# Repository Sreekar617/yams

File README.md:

## Yet Another Metronome by Sreekar  

Usually when I'm practicing my violin, I like to do a lot of metronome work to keep myself on tempo. However, neither my phone nor my laptop can be heard above the sound of the violin, and it's generally not a good idea to practice quieter because you practice the way you perform.  

Up until this point, my solution was to use the metronome on a Roland Digital Piano, since they're super loud and available for use at my school, where I do most of my practice. The problem is, I don't always practice in the practice rooms, and even then, the rooms with the piano aren't always available.  

My solution is to make a small, portable metronome that can stil get loud enough to hear over my violin playing. The device contains a piezo buzzer, a single Neopixel for visual feedback, an OLED to see the current BPM, and a rotary encoder to change the BPM. To keep things light and small, it's powered by a XIAO RP2040. 

PCB                             |  PCB + Case
:------------------------------:|:---------------------------------:
| 

BOM:
| Id | Designator | Footprint                                      | Quantity | Designation           | Supplier and ref | Link                                                                     |
| -- | ---------- | ---------------------------------------------- | -------- | --------------------- | ---------------- | ------------------------------------------------------------------------ |
| 1  | D1         | LED_SK6812MINI_PLCC4_3.5x3.5mm_P1.75mm         | 1        | SK6812MINI            | C5149201         | https://jlcpcb.com/partdetail/OPSCOOptoelectronics-SK6812MINIE/C5149201  |
| 2  | Q1         | SOT-23                                         | 1        | Q_NPN_BEC             | C2150            | https://jlcpcb.com/partdetail/2507-SS8050_RANGE_200_350/C2150            |
| 3  | J1         | OLED_128x32                                    | 1        | OLED_128x32           | C5248081         | https://jlcpcb.com/partdetail/HS-HS91L02W2C01/C5248081                   |
| 4  | SW1        | RotaryEncoder_Alps_EC11E-Switch_Vertical_H20mm | 1        | RotaryEncoder_Switch  | C202365          | https://jlcpcb.com/partdetail/ALPSALPINE-EC11E18244AU/C202365            |
| 5  | R1         | R_0603_1608Metric                              | 1        | 300Ω                  | C23025           | https://jlcpcb.com/partdetail/23752-0603WAF3000T5E/C23025                |
| 6  | R2         | R_0603_1608Metric                              | 1        | 1000Ω                 | C51218           | https://jlcpcb.com/partdetail/52231-0603WAD1001T5E/C51218                |
| 7  | U1         | XIAO-Generic-Hybrid-14P-2.54-21X17.8MM         | 1        | MOUDLE-SEEEDUINO-XIAO |                  | https://www.seeedstudio.com/XIAO-RP2040-v1-0-p-5026.html                 |
| 8  | LS1        | Buzzer_Murata_PKLCS1212E                       | 1        | PKLCS1212E4001-R1     | C113159          | https://jlcpcb.com/partdetail/MurataElectronics-PKLCS1212E4001R1/C113159 |
| 9  | --         | --                                             | 4        | M3x20mm Screws        | Generic          | Source locally                                                           |
| 10 | --         | --                                             | 1        | M3x12mm Screw         | Generic          | Source locally                                                           |
| 11 | --         | --                                             | 5        | M3 Nuts               | Generic          | Source locally                                                           |
| 12 | --         | --                                             | 1        | Bottom Case           | Generic          | Print with Legion                                                        |
| 13 | --         | --                                             | 1        | Top Case              | Generic          | Print with Legion                                                        |
| 14 | --         | --                                             | 1        | PCB                   | JLCPCB           | Order from JLCPCB                                                        |

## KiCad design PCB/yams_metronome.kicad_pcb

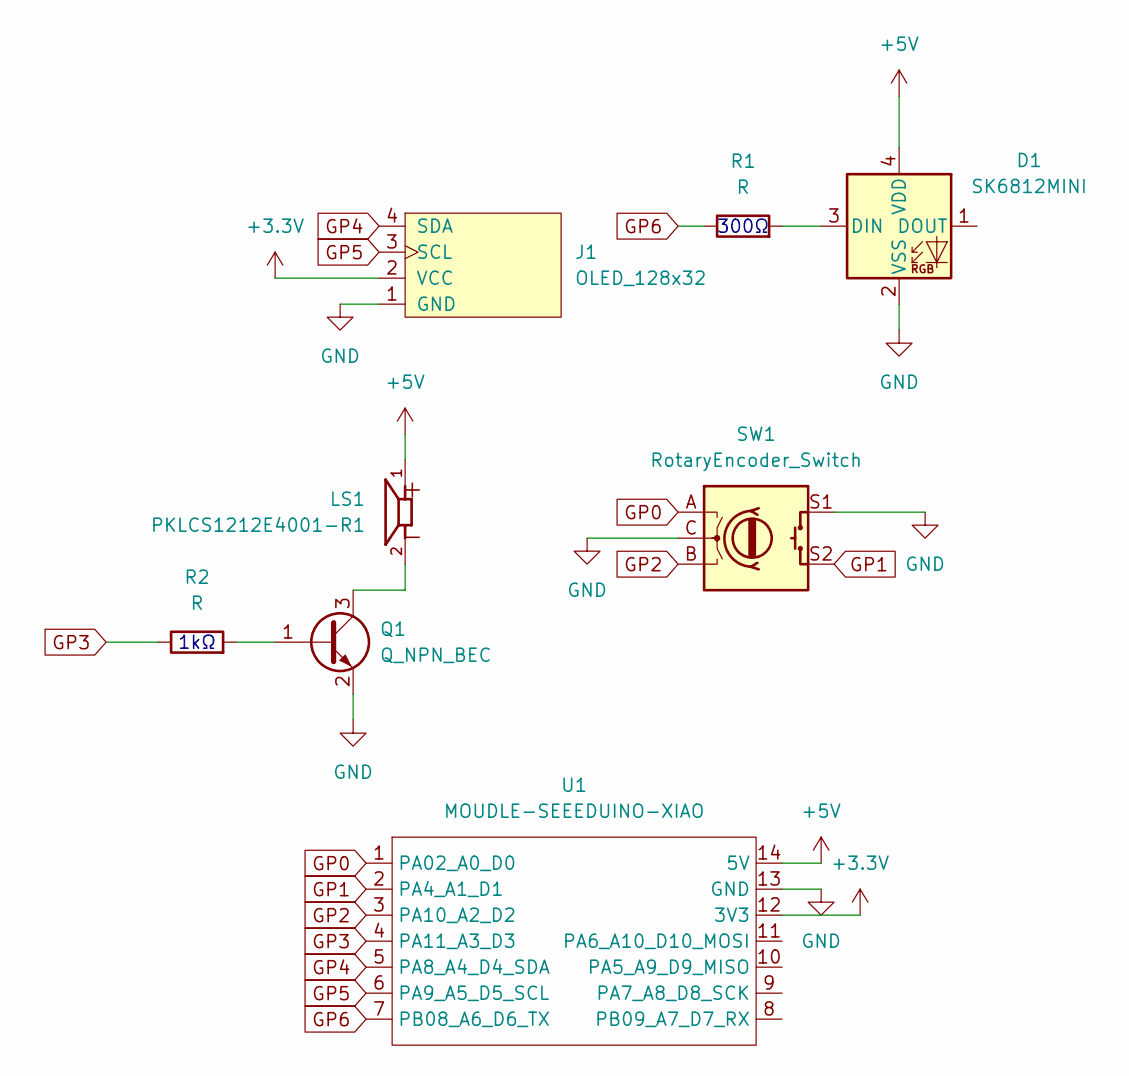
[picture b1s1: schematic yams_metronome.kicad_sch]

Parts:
D1: SK6812MINI; LED_SK6812MINI_PLCC4_3.5x3.5mm_P1.75mm
J1: OLED_128x32
LS1: PKLCS1212E4001-R1; Buzzer_Murata_PKLCS1212E; PARTREV January 22, 2018
Q1: Q_NPN_BEC; SOT-23
R1, R2: R; R_0603_1608Metric
SW1: RotaryEncoder_Switch; RotaryEncoder_Alps_EC11E-Switch_Vertical_H20mm
U1: MOUDLE-SEEEDUINO-XIAO; XIAO-Generic-Hybrid-14P-2.54-21X17.8MM

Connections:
+3.3V: J1.2 (VCC), U1.12 (3V3)
+5V: D1.4 (VDD), LS1.1, U1.14 (5V)
GND: D1.2 (VSS), J1.1 (GND), Q1.2 (E), SW1.C, SW1.S1, U1.13 (GND)
GP0: SW1.A, U1.1 (PA02_A0_D0)
GP1: SW1.S2, U1.2 (PA4_A1_D1)
GP2: SW1.B, U1.3 (PA10_A2_D2)
GP3: R2.1, U1.4 (PA11_A3_D3)
GP4: J1.4 (SDA), U1.5 (PA8_A4_D4_SDA)
GP5: J1.3 (SCL), U1.6 (PA9_A5_D5_SCL)
GP6: R1.1, U1.7 (PB08_A6_D6_TX)
unnamed: D1.3 (DIN), R1.2
unnamed: Q1.1 (B), R2.2
unnamed: LS1.2, Q1.3 (C)

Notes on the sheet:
300Ω
1kΩ

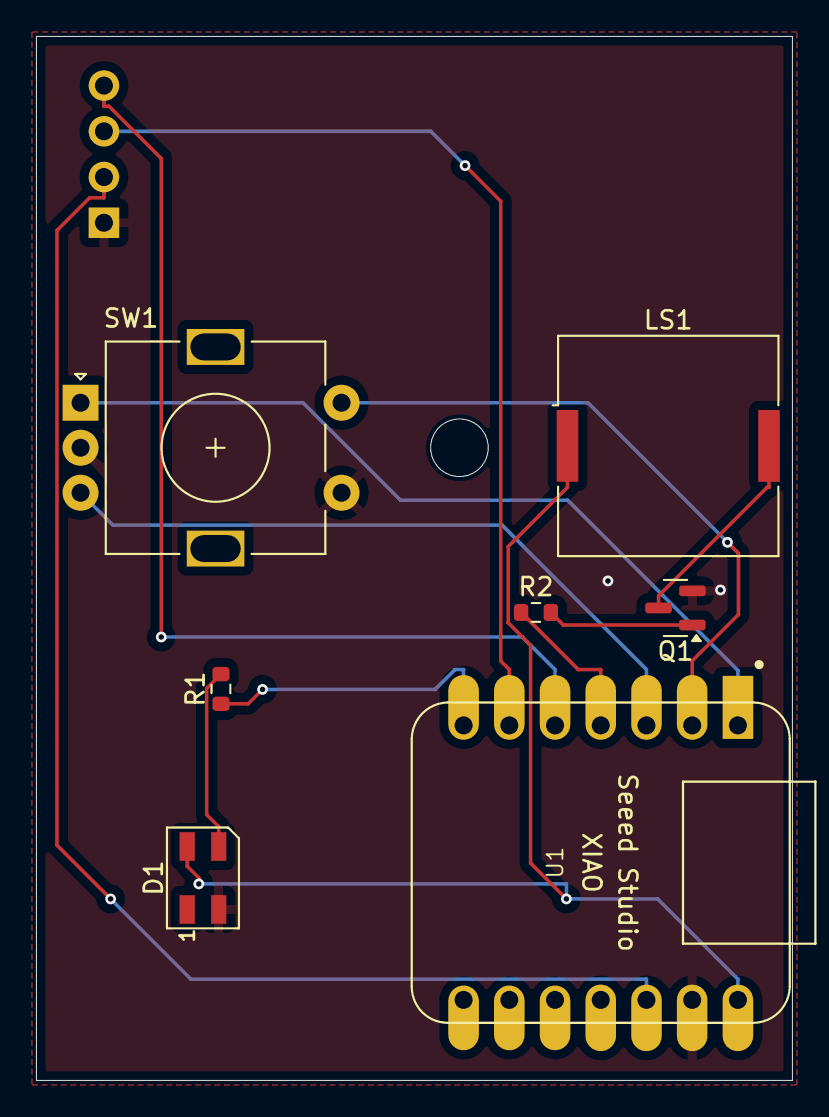
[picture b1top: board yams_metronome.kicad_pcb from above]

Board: 2 copper layers, 42.0 x 58.0 mm, 8 parts (0 on the bottom side), 13 nets.

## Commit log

2025-06-13 i think that's how you do it
2025-06-30 forgor
2025-07-02 commit from yesterday
2025-07-03 commit but not yet
2025-07-03 uploaded all the pcb and cad files
2025-07-07 added full model
